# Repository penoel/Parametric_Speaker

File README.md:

# Parametric_Speaker
This project is a simple parametric speaker design with a 64 transducer array and drive circuit.  The drive circuit is just a 555 that is modulated with an audio signal.  It also contains a filter and audio amplifier.  It is normally run into a PA amplifier to give the transducers a higher voltage, but all this could be integrated into one unit.

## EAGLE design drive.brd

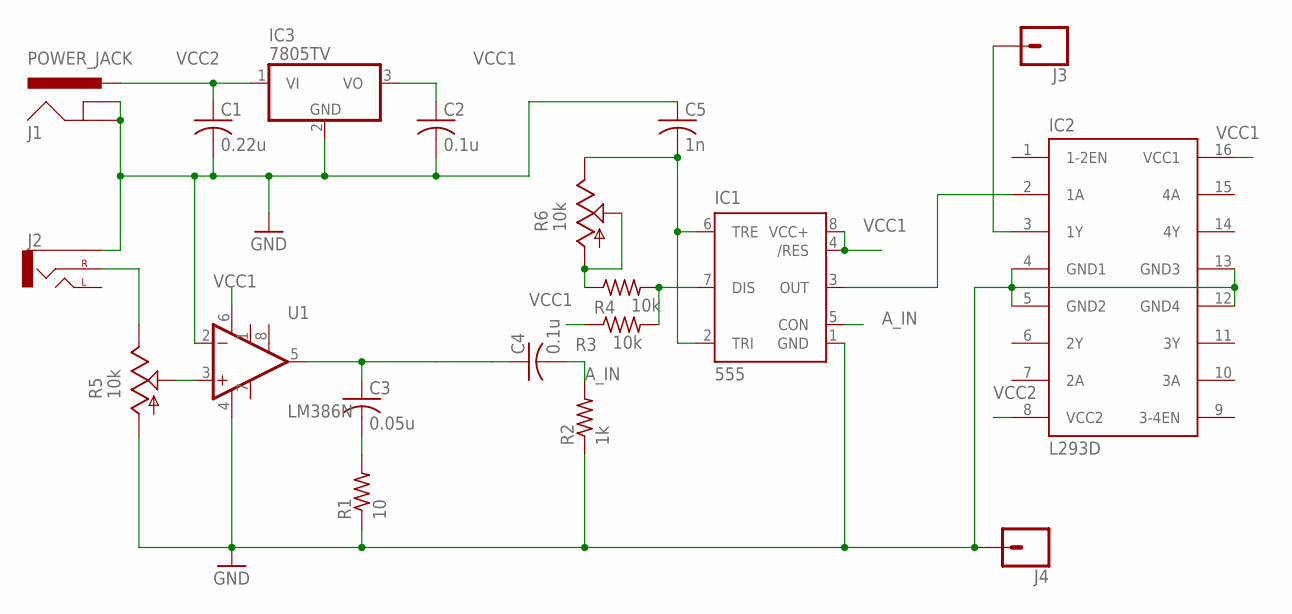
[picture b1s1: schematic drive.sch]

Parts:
C1: 0.22u; C025-030X050
C2, C4: 0.1u; C025-030X050
C3: 0.05u; C025-030X050
C5: 1n; C025-030X050
IC1: 555; DIP08
IC2: L293D; DIL16
IC3: 7805TV; TO220V
J1: POWER_JACK; POWER_JACK_PTH
J2: AUDIO_JACK_2.5MMSPECIAL_POGO_PINS; STEREOJACK2.5MM_SPECIAL_POGOPINS
J3, J4: CONN_01SMTSO-256-ET-0.165DIA; SMTSO-256-ET-0.165DIA
R1: 10; 0207/10
R2: 1k; 0207/10
R3, R4: 10k; 0207/10
R5, R6: 10k; CA6V
U1: LM386N; DIP08

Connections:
A_IN: C4.2, IC1.5 (CON), R2.2
GND: C1.2, C2.2, C5.1, IC1.1 (GND), IC2.4 (GND1), IC2.5 (GND2), IC2.12 (GND4), IC2.13 (GND3), IC3.2 (GND), J1.GND, J1.GNDBREAK, J2.RING1 (SLEEVE), J4.P$1, R1.1, R2.1, R5.A, U1.2 (-IN), U1.4 (V-)
unnamed: J2.TIP (RIGHT), R5.E
unnamed: IC1.7 (DIS), R3.2, R4.2
unnamed: R5.S, U1.3 (+IN)
unnamed: C3.1, C4.1, U1.5 (OUT)
unnamed: C3.2, R1.2
unnamed: C5.2, IC1.2 (TRI), IC1.6 (TRE), R6.E
unnamed: IC1.3 (OUT), IC2.2 (1A)
unnamed: R4.1, R6.A, R6.S
unnamed: IC2.3 (1Y), J3.P$1
VCC1: C2.1, IC1.4 (/RES), IC1.8 (VCC+), IC2.16 (VCC1), IC3.3 (VO), R3.1, U1.6 (V+)
VCC2: C1.1, IC2.8 (VCC2), IC3.1 (VI), J1.PWR

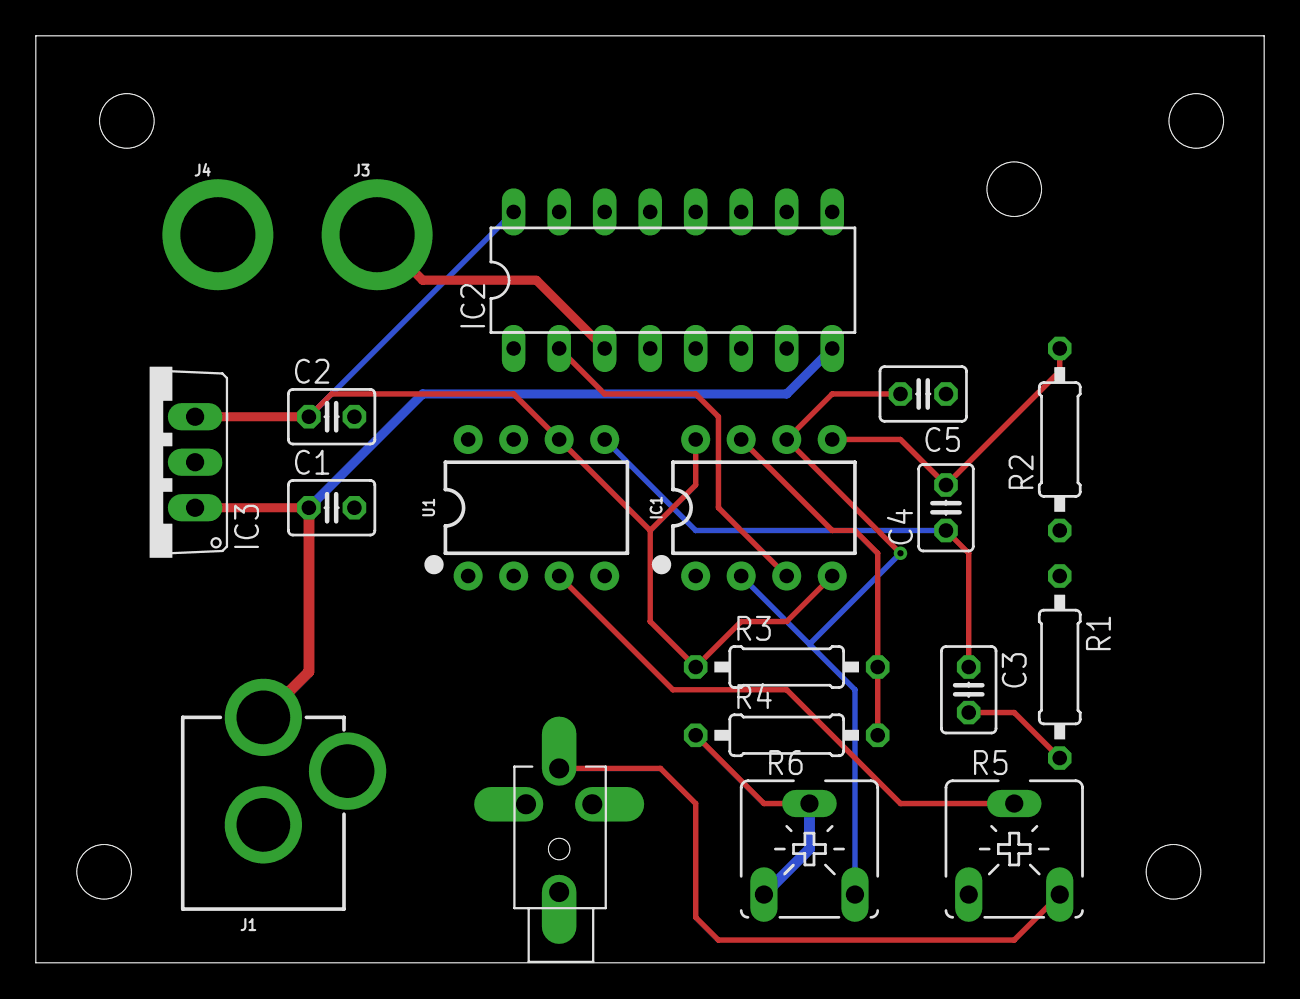
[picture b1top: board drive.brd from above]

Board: 2 copper layers, 68.6 x 51.7 mm, 19 parts (0 on the bottom side), 13 nets.

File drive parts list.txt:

Partlist exported from /Users/paulnoel/Downloads/Parametric_Speaker-master/drive.sch at 7/30/19 8:08 PM

Part Value      Device                            Package                          Description                                                                                                      MF MPN   OC_FARNELL OC_NEWARK PROD_ID    PROD_ID_ALT VALUE 
C1   0.22u      C-US025-030X050                   C025-030X050                     CAPACITOR, American symbol                                                                                                                                                  
C2   0.1u       C-US025-030X050                   C025-030X050                     CAPACITOR, American symbol                                                                                                                                                  
C3   0.05u      C-US025-030X050                   C025-030X050                     CAPACITOR, American symbol                                                                                                                                                  
C4   0.1u       C-US025-030X050                   C025-030X050                     CAPACITOR, American symbol                                                                                                                                                  
C5   1n         C-US025-030X050                   C025-030X050                     CAPACITOR, American symbol                                                                                                                                                  
IC1  555        555P                              DIP08                            General purpose bipolar Timer                                                                                                                  IC-09173   IC-09173    555   
IC2  L293D      L293D                             DIL16                            PUSH-PULL 4 CHANNEL DRIVER                                                                                          L293D 9589619    56P8249                                
IC3  7805TV     7805TV                            TO220V                           Positive VOLTAGE REGULATOR                                                                                                                                                  
J1   POWER_JACK POWER_JACK                        POWER_JACK_PTH                   Power Jack Connector                                                                                                                           CONN-08197                   
J2              AUDIO_JACK_2.5MMSPECIAL_POGO_PINS STEREOJACK2.5MM_SPECIAL_POGOPINS Audio Jack                                                                                                                                                                  
J3              CONN_01SMTSO-256-ET-0.165DIA      SMTSO-256-ET-0.165DIA            Single connection point. Often used as Generic Header-pin footprint for 0.1 inch spaced/style header connections                               HW-08694                     
J4              CONN_01SMTSO-256-ET-0.165DIA      SMTSO-256-ET-0.165DIA            Single connection point. Often used as Generic Header-pin footprint for 0.1 inch spaced/style header connections                               HW-08694                     
R1   10         R-US_0207/10                      0207/10                          RESISTOR, American symbol                                                                                                                                                   
R2   1k         R-US_0207/10                      0207/10                          RESISTOR, American symbol                                                                                                                                                   
R3   8.2k-10k   R-US_0207/10                      0207/10                          May need adjustment for 40kHz carrier                                                                                                                                                  
R4   10k        R-US_0207/10                      0207/10                          RESISTOR, American symbol                                                                                                                                                   
R5   10k        TRIM_US-CA6V                      CA6V                             POTENTIOMETER                                                                                                                                                               
R6   10k        TRIM_US-CA6V                      CA6V                             POTENTIOMETER                                                                                                                                                               
U1   LM386N     LM386                             DIP08                            low voltage audio power amplifier                                                                                                              IC-10899               LM386N

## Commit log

2019-07-11 Create description
2019-07-11 Add files via upload
    64 transducers in an individual accessible array

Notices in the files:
parts and their libraries:
SparkFun-IC-Special-Function: Licensing: Creative Commons ShareAlike 4.0 International - https://creativecommons.org/licenses/by-sa/4.0
